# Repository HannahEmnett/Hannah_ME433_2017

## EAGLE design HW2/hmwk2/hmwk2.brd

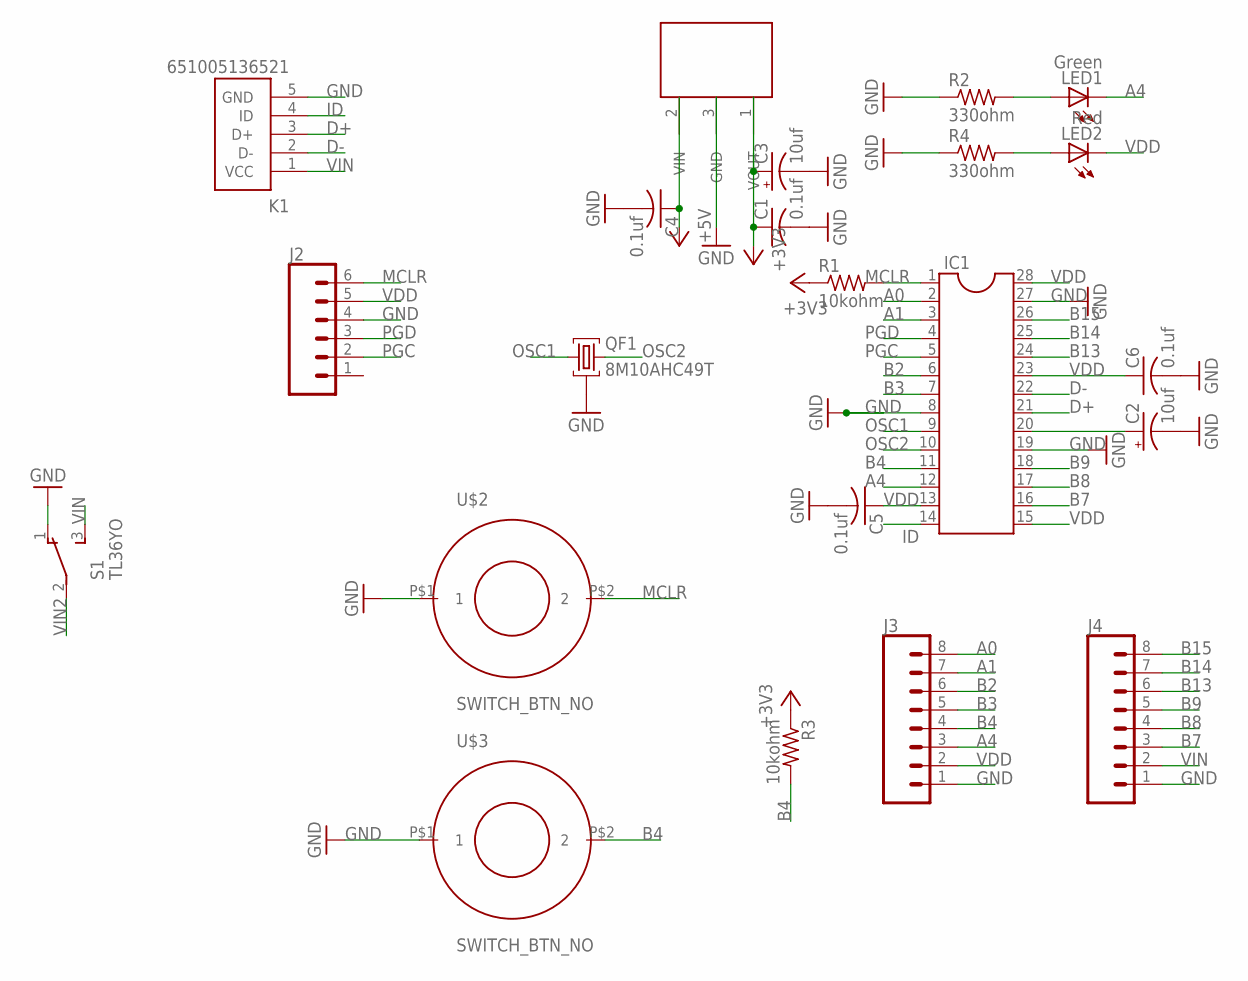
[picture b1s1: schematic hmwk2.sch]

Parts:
C1, C4, C5, C6: 0.1uf; C025-025X050
C2, C3: 10uf; E5-5
IC1: DIL28-3
J2: CONN_06SILK_FEMALE_PTH; 1X06
J3, J4: CONN_08"; 1X08
K1: 651005136521
LED1: Green; LED3MM
LED2: Red; LED3MM
QF1: 8M10AHC49T; HC49U
R1, R3: 10kohm; 0207/10
R2, R4: 330ohm; 0207/10
S1: TL36YO; TL3XYO
U$1: TO92
U$2, U$3: SWITCH_BTN_NO; BTN_2

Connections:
+3V3: C1.1, C3.+, R1.1, R3.1, U$1.1 (VOUT)
A0: IC1.2, J3.8
A1: IC1.3, J3.7
A4: IC1.12, J3.3, LED1.K (C)
B2: IC1.6, J3.6
B3: IC1.7, J3.5
B4: IC1.11, J3.4, R3.2, U$3.P$2 (2)
B7: IC1.16, J4.3
B8: IC1.17, J4.4
B9: IC1.18, J4.5
B13: IC1.24, J4.6
B14: IC1.25, J4.7
B15: IC1.26, J4.8
D+: IC1.21, K1.3 (D+)
D-: IC1.22, K1.2 (D-)
GND: C1.2, C2.-, C3.-, C4.2, C5.2, C6.2, IC1.8, IC1.19, IC1.27, J2.4, J3.1, J4.1, K1.5 (GND), QF1.2, R2.1, R4.1, S1.1 (O), U$1.3 (GND), U$2.P$1 (1), U$3.P$1 (1)
ID: IC1.14, K1.4 (ID)
MCLR: IC1.1, J2.6, R1.2, U$2.P$2 (2)
unnamed: LED1.A, R2.2
unnamed: C2.+, IC1.20
unnamed: LED2.A, R4.2
OSC1: IC1.9, QF1.1
OSC2: IC1.10, QF1.3
PGC: IC1.5, J2.2
PGD: IC1.4, J2.3
VDD: C5.1, C6.1, IC1.13, IC1.15, IC1.23, IC1.28, J2.5, J3.2, LED2.K (C)
VIN: J4.2, K1.1 (VCC), S1.3 (S)
VIN2: C4.1, S1.2, U$1.2 (VIN)

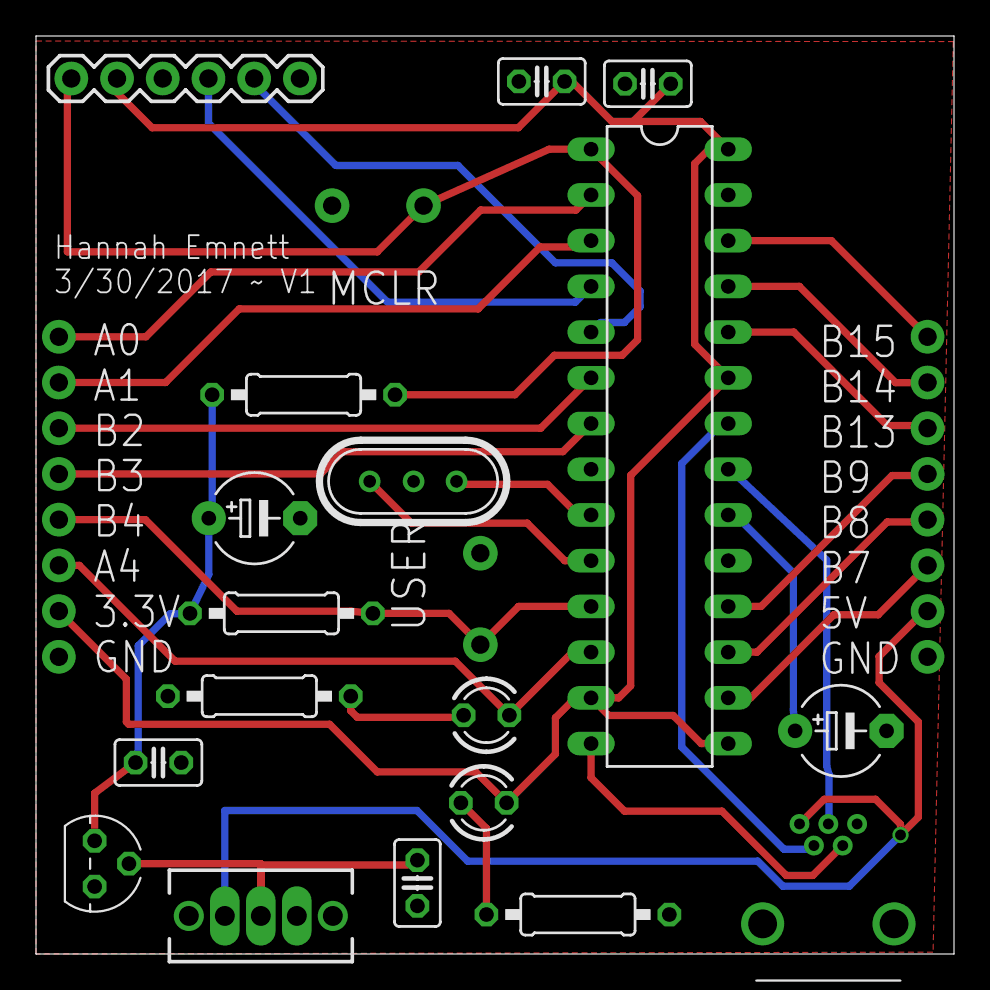
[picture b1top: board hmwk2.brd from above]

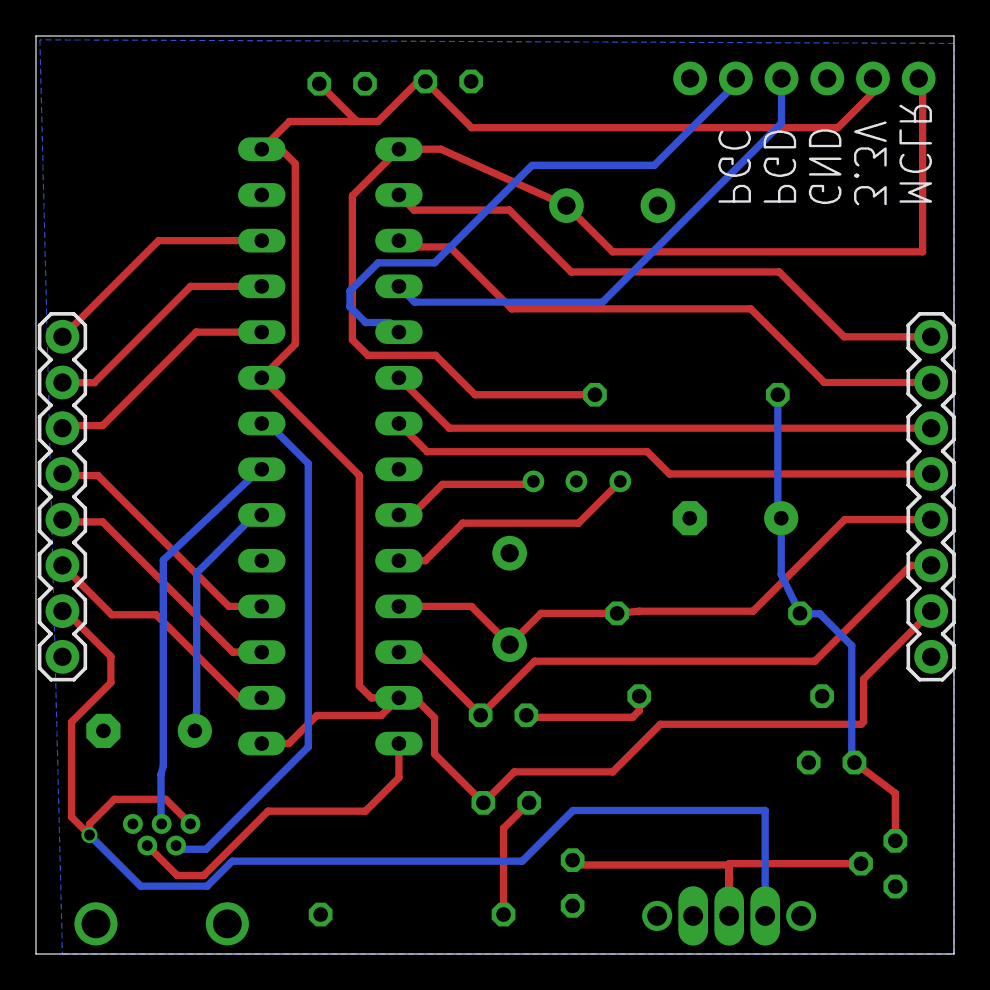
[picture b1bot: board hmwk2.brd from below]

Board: 2 copper layers, 51.0 x 51.0 mm, 22 parts (2 on the bottom side), 28 nets.

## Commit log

2017-03-28 added hmwk1
2017-03-28 images
2017-03-28 programmed a bunch
2017-03-28 finished project and adjusted for 1khz
2017-03-28 added schematic pic
2017-03-28 something else changed idk
2017-03-31 all of hmwk 2 oops
2017-04-04 updated board
2017-04-04 gerber files
2017-04-04 flipped slide switch because of reasons
2017-04-04 new gerber files
2017-04-06 started hw4
2017-04-10 worked on spidac
2017-04-11 tried again
2017-04-11 added hmwk5
2017-04-11 fininished hmwk 4
2017-04-11 all hmwk 4 and started hmwk5
2017-04-12 i try and i try
2017-04-13 worst day of my life
2017-04-13 finally finished yay thank god
2017-04-16 hello lcd world
2017-04-16 counting counting
2017-04-17 added fps for gigs
2017-04-20 imu is chill
2017-04-22 imu stuff
2017-04-22 compiled with harmony
2017-04-26 started usb cdc
2017-04-26 finished cdc
2017-04-26 added vid
2017-05-13 i hate mice
2017-05-13 camera app
2017-05-14 did the usb phone thing
2017-05-22 addded wheel et all
2017-06-07 all the things
2017-06-08 all the things again!
2017-06-09 finally finished
2018-02-15 Set theme jekyll-theme-cayman
